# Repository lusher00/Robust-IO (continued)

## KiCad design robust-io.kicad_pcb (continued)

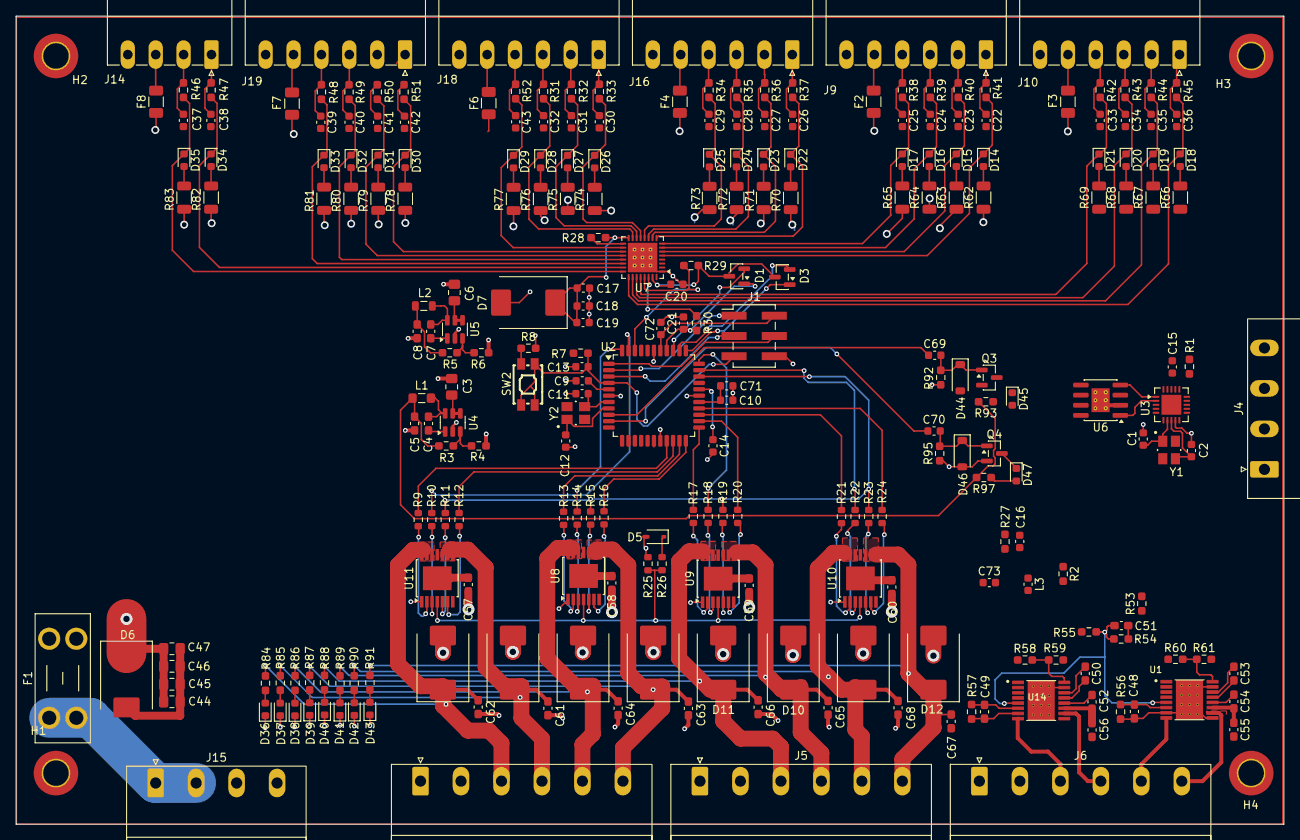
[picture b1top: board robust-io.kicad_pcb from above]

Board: 4 copper layers, 159.1 x 101.4 mm, 258 parts (0 on the bottom side), 184 nets.

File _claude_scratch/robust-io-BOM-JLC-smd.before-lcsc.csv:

Comment,Designator,Footprint,LCSC Part #
22pF,"C1,C2,C11,C12",C_0603_1608Metric,C1653
2.2uF 50V,"C3,C6,C46",C_0805_2012Metric,C377773
100nF 50V,"C4,C7,C9,C10,C13,C14,C15,C18,C20,C21,C22,C23,C24,C25,C26,C27,C28,C29,C30,C31,C32,C33,C34,C35,C36,C37,C38,C39,C40,C41,C42,C43,C48,C49,C51,C52,C54,C55,C56,C57,C58,C59,C60,C61,C62,C63,C64,C65,C66,C67,C68,C71,C72,C73",C_0603_1608Metric,C14663
22uF,"C5,C8",C_0603_1608Metric,
1nF,"C16,C19",C_0603_1608Metric,C1588
10uF 50V,C17,C_0805_2012Metric,C440198
100uF 50V,"C44,C45",CP_Elec_8x10,
100nF 50V,C47,C_0805_2012Metric,
22nF,"C50,C53",C_0603_1608Metric,C21122
10nF,"C69,C70",C_0603_1608Metric,C57112
BAT54C,"D1,D3",SOT-23,
B560C,"D2,D4,D8,D9,D10,D11,D12,D13",D_SMC,
BZX384C6V8,D5,D_SOD-323,
SMDJ24A,D6,D_SMC,
B340,D7,D_SMC,
LED,"D14,D15,D16,D17,D18,D19,D20,D21,D22,D23,D24,D25,D26,D27,D28,D29,D30,D31,D32,D33,D34,D35,D36,D37,D38,D39,D40,D41,D42,D43,D45,D47",LED_0603_1608Metric,
1N4148W,"D44,D46",D_SOD-123,
SP0502BAHT,D48,SOT-23,
Polyfuse,"F2,F3,F4,F6,F7,F8",Fuse_1206_3216Metric,
AVR-ISP-6,J1,PinHeader_2x03_P2.54mm_Vertical_SMD,
6.8uH,L1,L_0805_2012Metric,
18uH,L2,L_0805_2012Metric,
10uH,L3,C_0603_1608Metric,
2N7002,"Q3,Q4",SOT-23,
10k,"R1,R7,R28,R29,R53",R_0603_1608Metric,
120,R2,R_0603_1608Metric,
51k,R3,R_0603_1608Metric,
22.1k,"R4,R6",R_0603_1608Metric,
88.7k,R5,R_0603_1608Metric,
330,"R8,R93,R97",R_0603_1608Metric,
4.7k,"R9,R10,R11,R12,R13,R14,R15,R16,R17,R18,R19,R20,R21,R22,R23,R24,R26,R27",R_0603_1608Metric,
750,R25,R_0603_1608Metric,
1k,"R30,R98,R99",R_0603_1608Metric,
100,"R31,R32,R33,R34,R35,R36,R37,R38,R39,R40,R41,R42,R43,R44,R45,R46,R47,R48,R49,R50,R51,R52",R_0603_1608Metric,
16.2k 1%,R54,R_0603_1608Metric,
10k 1%,R55,R_0603_1608Metric,
1.5k 1%,"R56,R57",R_0603_1608Metric,
0,"R59,R61",R_0603_1608Metric,
2.2k,"R62,R63,R64,R65,R66,R67,R68,R69,R70,R71,R72,R73,R74,R75,R76,R77,R78,R79,R80,R81,R82,R83",R_1206_3216Metric,
2.2k,"R84,R85,R86,R87,R88,R89,R90,R91",R_0603_1608Metric,
100k,"R92,R95",R_0603_1608Metric,
CHS-01TB,SW1,SW_DIP_SPSTx01_Slide_Copal_CHS-01B_W7.62mm_P1.27mm,
B3U-1000P,SW2,SW_SPST_B3U-1000P,
DRV8876,"U1,U14",IC_DRV8876PWPR,
ATmega1284P-A,U2,TQFP-44_10x10mm_P0.8mm,
MCP2515,U3,QFN-20-1EP_4x4mm_P0.5mm_EP2.5x2.5mm,
TPS5604,"U4,U5",SOT-23-6,
MCP2562-E-MF,U6,DFN-8-1EP_3x3mm_P0.65mm_EP1.6x2.56mm,
MC33978,U7,HSOP-32-1EP_7.5x11mm_P0.65mm_EP4.7x4.7mm,
BTS7008,"U8,U9,U10,U11",TSSOP-14-1EP_4.4x5mm_P0.65mm,
16MHz,Y1,WE-XTAL_CFPX-180,
12MHz,Y2,WE-XTAL_CFPX-180,

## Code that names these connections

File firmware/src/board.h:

/* Robust IO rev A - pin map and board constants.
 * Source: rev A netlist (U2 pad nets). See ../DESIGN.md section 2. */
#ifndef BOARD_H
#define BOARD_H

#include <avr/io.h>

#ifndef F_CPU
#define F_CPU            12000000UL   /* Y2 */
#endif
#define MCP2515_F_OSC    16000000UL   /* Y1 */
#define UART_BAUD        38400UL

/* Port A */
#define ADC_CH_AMUX      0            /* PA0  MC33978 AMUX */
#define ADC_CH_ISENSE    1            /* PA1  BTS7008 IS, shared */
#define ADC_CH_IPROPI0   2            /* PA2  motor 0 current */
#define ADC_CH_IPROPI1   3            /* PA3  motor 1 current */
#define DEN2_BIT         PA4          /* U9,  outputs 4, 5 */
#define DEN3_BIT         PA5          /* U10, outputs 6, 7 */
#define DSEL_BIT         PA6          /* shared, low = channel 0 of each device */
#define NSLEEP_BIT       PA7          /* DRV8876 nSLEEP, shared */

/* Port B */
#define CS_CAN_BIT       PB0
#define CS_IN_BIT        PB1
#define INT_IN_BIT       PB2          /* INT2, MC33978 INT_B, active low */
#define DEN0_BIT         PB3          /* U11, outputs 0, 1 */
#define DEN1_BIT         PB4          /* U8,  outputs 2, 3. Also SPI SS: keep as output */
#define SPI_MOSI_BIT     PB5
#define SPI_MISO_BIT     PB6
#define SPI_SCK_BIT      PB7

/* Port C: DRV_OUT0..7 on PC0..PC7, high = output on.
 * PC2..PC5 are JTAG pins: JTAGEN fuse must be unprogrammed. */
#define HSD_COUNT        8

/* Port D */
#define INT_CAN_BIT      PD2          /* INT0, MCP2515 INT, active low */
#define FAULTM_BIT       PD3          /* INT1, DRV8876 nFAULT, shared, active low */
#define PH_M0_BIT        PD4
#define EN_M0_BIT        PD5          /* OC1A */
#define PH_M1_BIT        PD6
#define EN_M1_BIT        PD7          /* OC2A */

/* Reset-state port values: everything off, chip selects high. */
#define PORTA_INIT       0x00
#define DDRA_INIT        ((1<<DEN2_BIT)|(1<<DEN3_BIT)|(1<<DSEL_BIT)|(1<<NSLEEP_BIT))
#define PORTB_INIT       ((1<<CS_CAN_BIT)|(1<<CS_IN_BIT))
#define DDRB_INIT        ((1<<CS_CAN_BIT)|(1<<CS_IN_BIT)|(1<<DEN0_BIT)|(1<<DEN1_BIT)| \
                          (1<<SPI_MOSI_BIT)|(1<<SPI_SCK_BIT))
#define PORTC_INIT       0x00
#define DDRC_INIT        0xFF
#define PORTD_INIT       ((1<<PD0)|(1<<PD1)|(1<<INT_CAN_BIT))   /* RX pull-up, TX idle high, INT pull-up */
#define DDRD_INIT        ((1<<PD1)|(1<<PH_M0_BIT)|(1<<EN_M0_BIT)|(1<<PH_M1_BIT)|(1<<EN_M1_BIT))

/* Scaling */
#define ADC_VREF_MV          3300UL   /* AVCC reference */
#define ISENSE_R_OHM         750UL    /* R25 */
#define BTS7008_KILIS        5400UL   /* datasheet typ; +/-4 % at 5.5 A, +/-30 % at 100 mA */
#define ISENSE_SETTLE_MS     2        /* datasheet worst case 0.4 ms at small load */
#define ISENSE_FAULT_MV      3000UL   /* fault current is >= 4.4 mA = 3.3 V on 750 ohm */
#define HSD_OFF_HIGH_MV      1000UL   /* off-state diagnosis current is 1.9..3.5 mA = 1.4..2.6 V */
#define HSD_LIMIT_MA_DEFAULT  5000     /* software trip level per output; set per channel with 'limit' */
#define HSD_TRIP_MS_DEFAULT  100      /* time over the limit before the output is switched off */
#define IPROPI_R_OHM         1500UL   /* 1000 uA per amp into 1.5k = 1.5 V per amp */
#define MOTOR_ITRIP_MA       1360     /* set by VREF divider, not firmware */

/* Configuration defaults (see app/config.c; all can be changed and saved) */
#define CFG_DEFAULT_NODE        0
#define CFG_DEFAULT_RATE_KBIT   250
#define CFG_DEFAULT_TIMEOUT_MS  500      /* host timeout, 0 disables */
#define CFG_DEFAULT_DEBOUNCE_MS 20
#define CFG_DEFAULT_WET_MA      16       /* MC33978 wetting current, power-on default */
#define CFG_DEFAULT_SLEW        10       /* motor duty change, percent per 10 ms */
#define CFG_DEFAULT_IDLE_MS     1000     /* motor drivers sleep after this long at zero */

/* MC33978 */
#define MC33978_INPUTS       22       /* bits 0..13 = SG0..SG13, bits 14..21 = SP0..SP7 */
#define MC33978_SPI_MODE     0        /* CHECK at bring-up: datasheet text says latch on rising edge.
                                         If the SPI check fails, try mode 1. */
#define MCP2515_SPI_MODE     0

#endif
